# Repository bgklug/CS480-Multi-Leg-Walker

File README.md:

# CS480-Multi-Leg-Walker
For CS 480 Project 2

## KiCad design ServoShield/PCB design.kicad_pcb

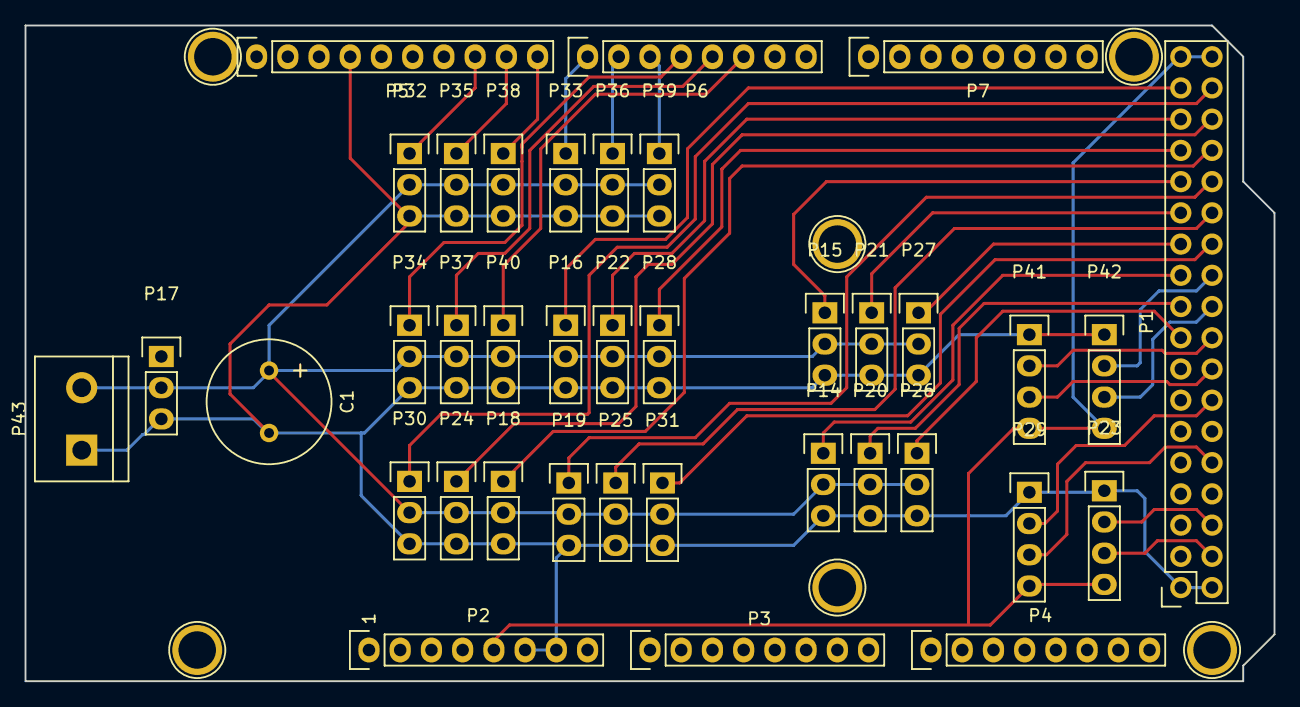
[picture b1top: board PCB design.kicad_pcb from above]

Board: 2 copper layers, 101.6 x 53.3 mm, 44 parts (0 on the bottom side), 35 nets.

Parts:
C1: CP1; Elko_vert_20x10mm_RM5
P1: Digital; Socket_Strip_Arduino_2x18
P2: Power; Socket_Strip_Arduino_1x08
P3, P4: Analog; Socket_Strip_Arduino_1x08
P5: PWM; Socket_Strip_Arduino_1x10
P6: PWM; Socket_Strip_Arduino_1x08
P7: Communication; Socket_Strip_Arduino_1x08
P8, P9, P10, P11, P12, P13: CONN_1; Arduino_1pin
P14, P15, P16, P17, P18, P19, P20, P21, P22, P24, P25, P26, P27, P28, P30, P31, P32, P33, P34, P35, P36, P37, P38, P39, P40: CONN_01X03; Pin_Header_Straight_1x03
P23, P29, P41, P42: CONN_01X04; Pin_Header_Straight_1x04
P43: CONN_01X02; bornier2

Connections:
+5V: P1.35, P1.36, P2.5, P23.4, P29.4, P41.4, P42.4
+6V: C1.1, P14.2, P15.2, P16.2, P17.2, P18.2, P19.2, P20.2, P21.2, P22.2, P24.2, P25.2, P26.2, P27.2, P28.2, P30.2, P31.2, P32.2, P33.2, P34.2, P35.2, P36.2, P37.2, P38.2, P39.2, P40.2, P43.2
/2(**): P6.6, P40.1
/3(**): P6.5, P37.1
/4(**): P6.4, P34.1
/5(**): P6.3, P39.1
/6(**): P6.2, P36.1
/7(**): P6.1, P33.1
/8(**): P5.10, P38.1
/9(**): P5.9, P35.1
/10(**): P5.8, P32.1
/22: P1.33, P16.1
/23: P1.34, P30.1
/24: P1.31, P22.1
/25: P1.32, P24.1
/26: P1.29, P28.1
/27: P1.30, P18.1
/28: P1.27, P15.1
/29: P1.28, P19.1
/30: P1.25, P21.1
/31: P1.26, P25.1
/32: P1.23, P27.1
/33: P1.24, P31.1
/34: P1.21, P14.1
/35: P1.22, P42.2
/36: P1.19, P20.1
/37: P1.20, P42.3
/38: P1.17, P26.1
/39: P1.18, P41.2
/41: P1.16, P41.3
/43: P1.14, P29.2
/47: P1.10, P29.3
/51(MOSI): P1.6, P23.2
/53(SS): P1.4, P23.3
GND: C1.2, P1.1, P1.2, P2.6, P2.7, P5.4, P14.3, P15.3, P16.3, P17.3, P18.3, P19.3, P20.3, P21.3, P22.3, P23.1, P24.3, P25.3, P26.3, P27.3, P28.3, P29.1, P30.3, P31.3, P32.3, P33.3, P34.3, P35.3, P36.3, P37.3, P38.3, P39.3, P40.3, P41.1, P42.1, P43.1

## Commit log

2015-11-07 Current code added
2015-11-10 removed junk files
2015-11-10 rm junk
2015-11-10 Uploading openscad and some code
2015-11-11 Fixed and added the full base to the polybot. The code is fully parametric. Also added servo backplate
2015-11-13 Added PCB files
    PCB has 24 servo, 4 ultrasonic sensor connection
2015-11-13 First draft of all of the mechanical parts
2015-11-15 adding body and arduino mount
2015-11-21 Updates to shit AM:
2015-11-24 latest changes
2015-11-24 in class modifications
2015-11-24 adding smaller body
2015-12-02 lots of minor modification to make parts fit better. All stls needed for one print and my GCODE were added to ONE LEG
2015-12-08 MultiWalker compiles
    Compiles but it appears the servos draw too many amps.
2015-12-09 Working Base code
2015-12-09 Now with few comments
2015-12-09 added somthing that might make it walk AM
2015-12-11 IT WORKS
2015-12-22 working code with movement
    Use a for walk left, w for walk forward, d for walk right, c for crouch,
    and s for stand
